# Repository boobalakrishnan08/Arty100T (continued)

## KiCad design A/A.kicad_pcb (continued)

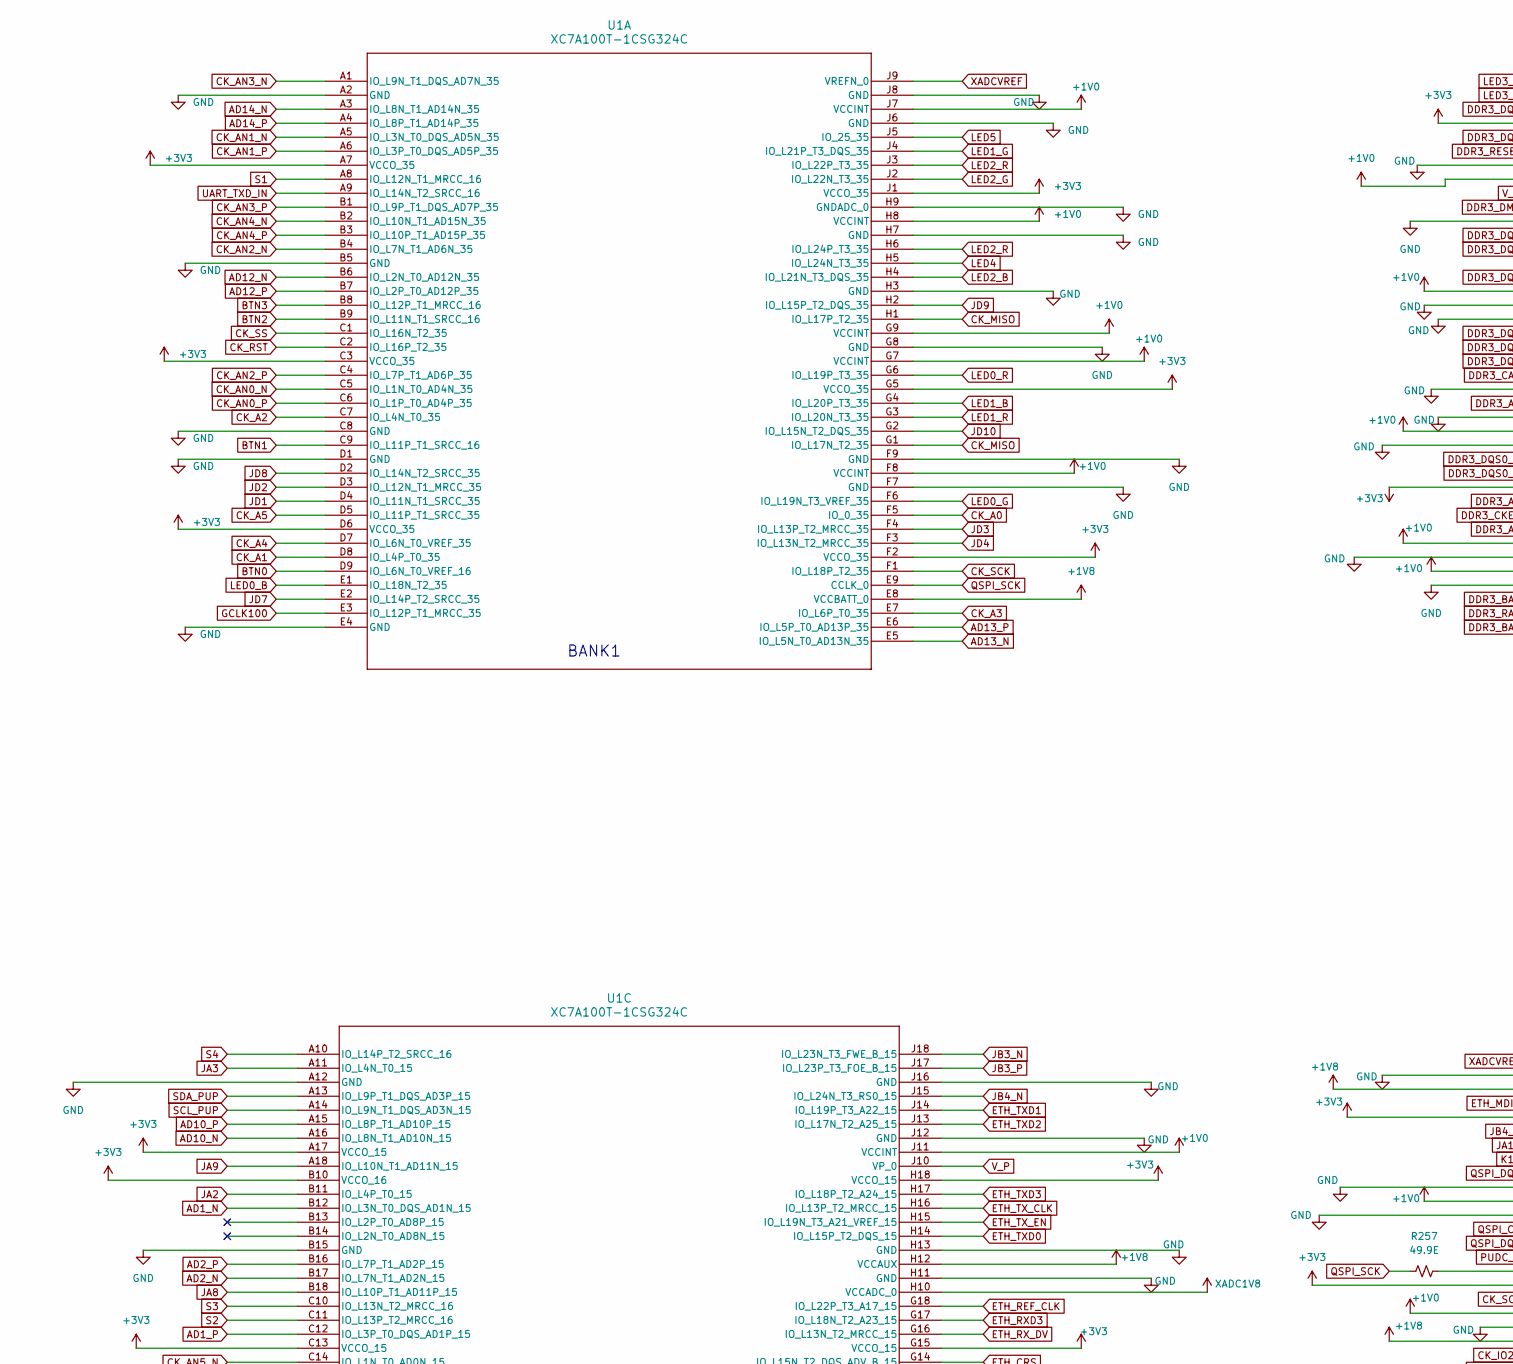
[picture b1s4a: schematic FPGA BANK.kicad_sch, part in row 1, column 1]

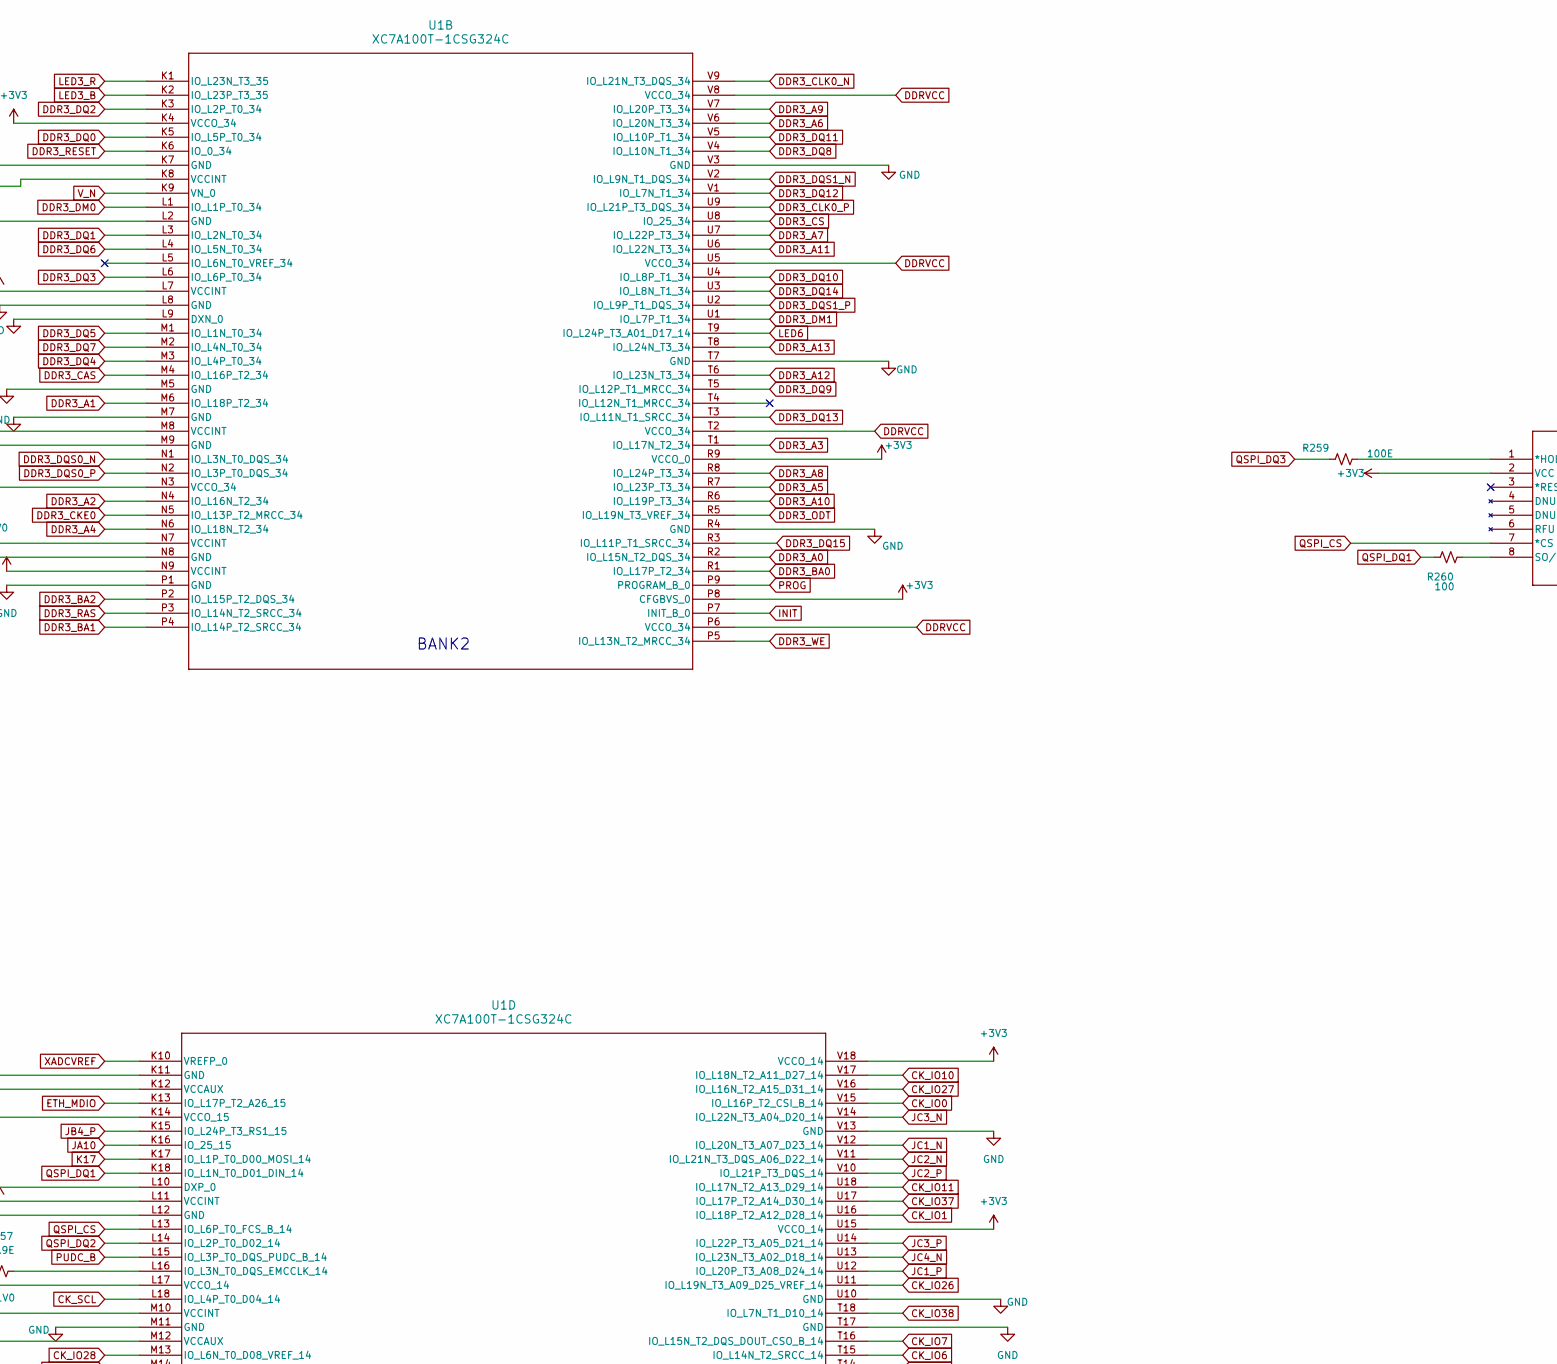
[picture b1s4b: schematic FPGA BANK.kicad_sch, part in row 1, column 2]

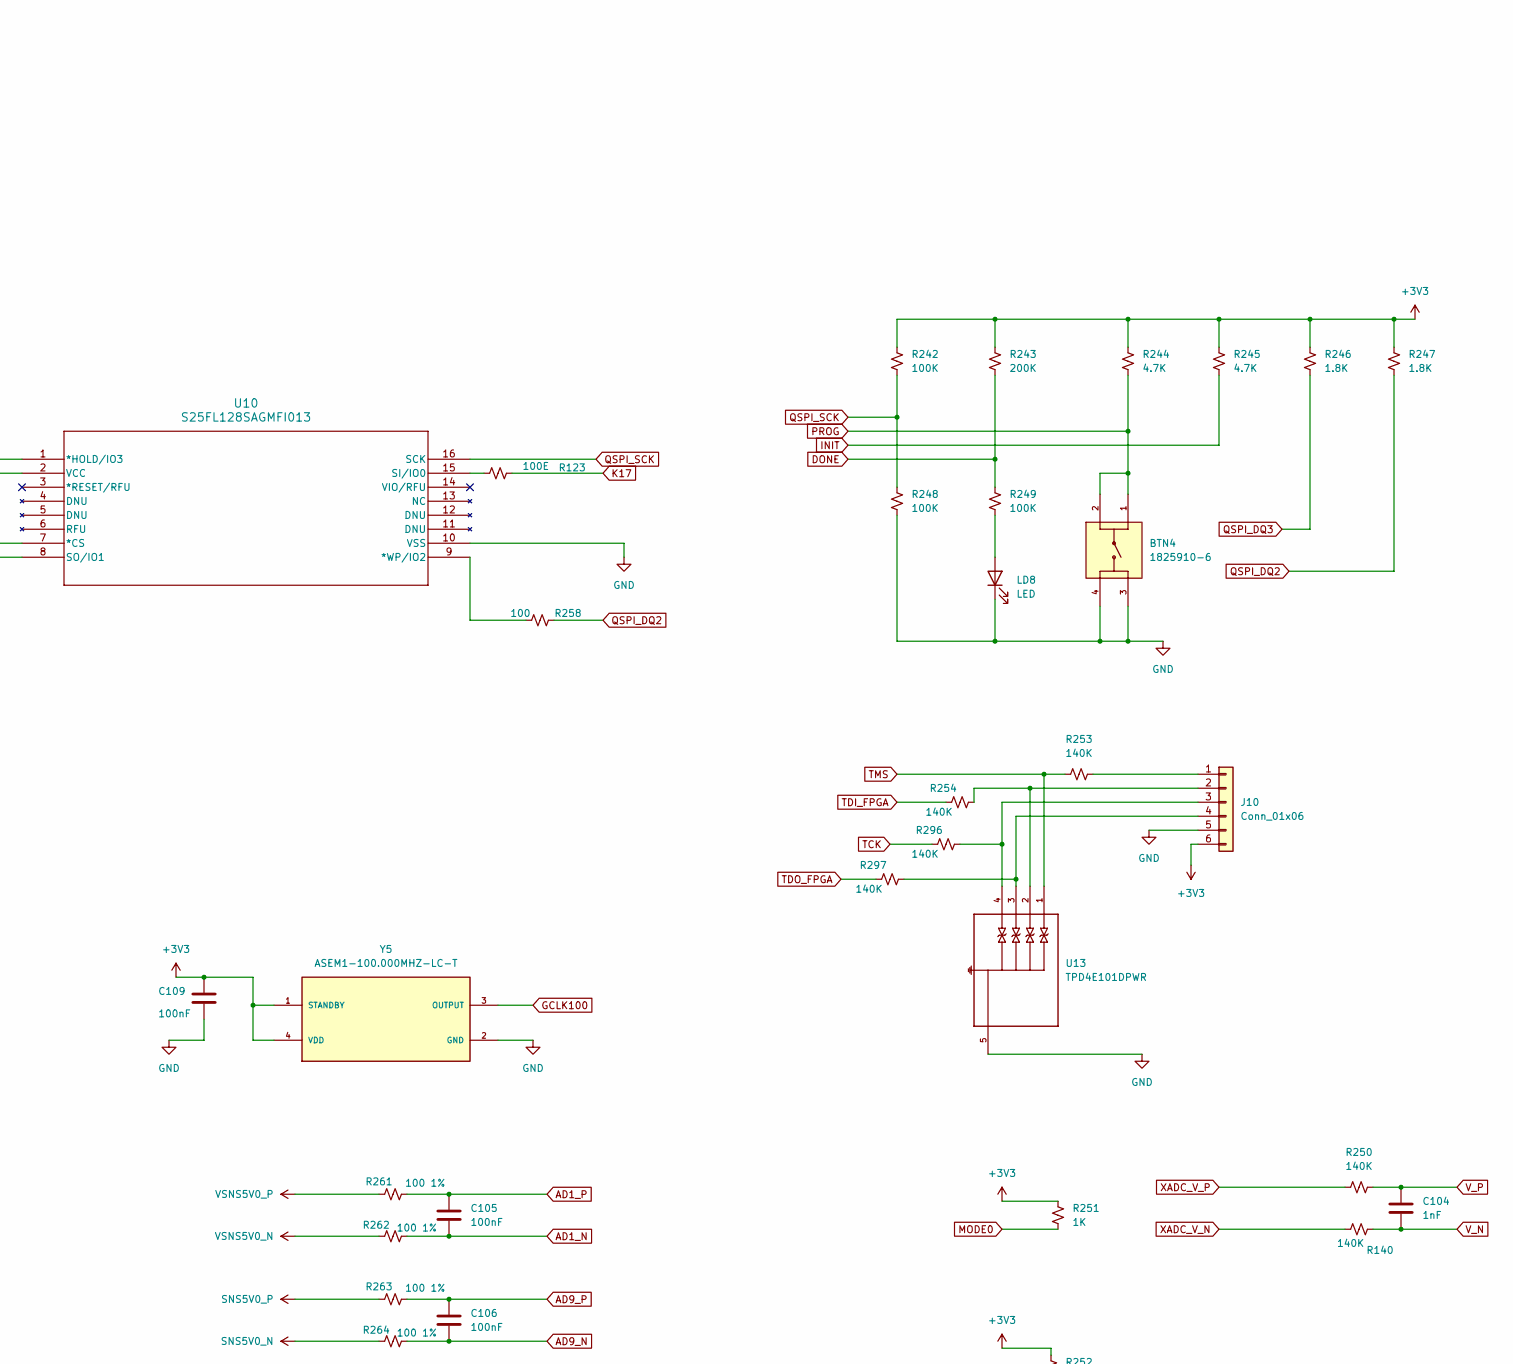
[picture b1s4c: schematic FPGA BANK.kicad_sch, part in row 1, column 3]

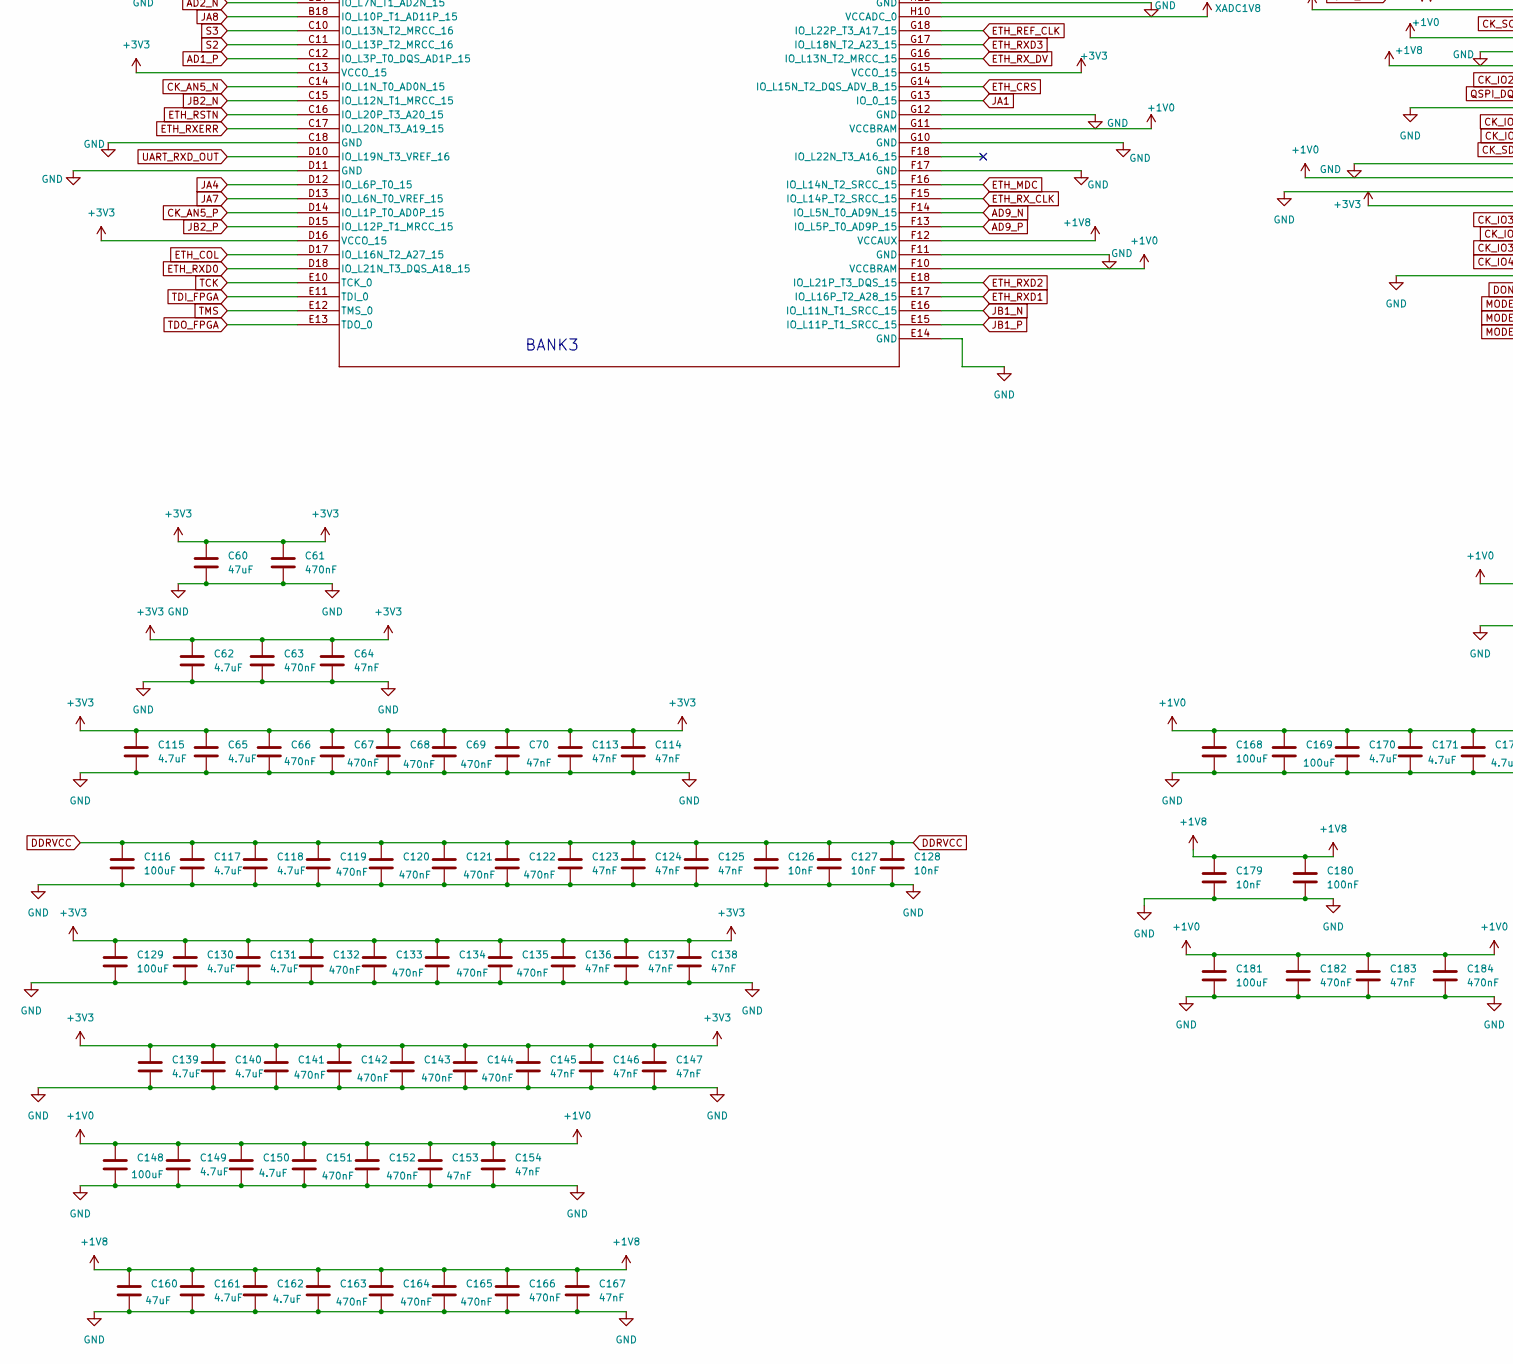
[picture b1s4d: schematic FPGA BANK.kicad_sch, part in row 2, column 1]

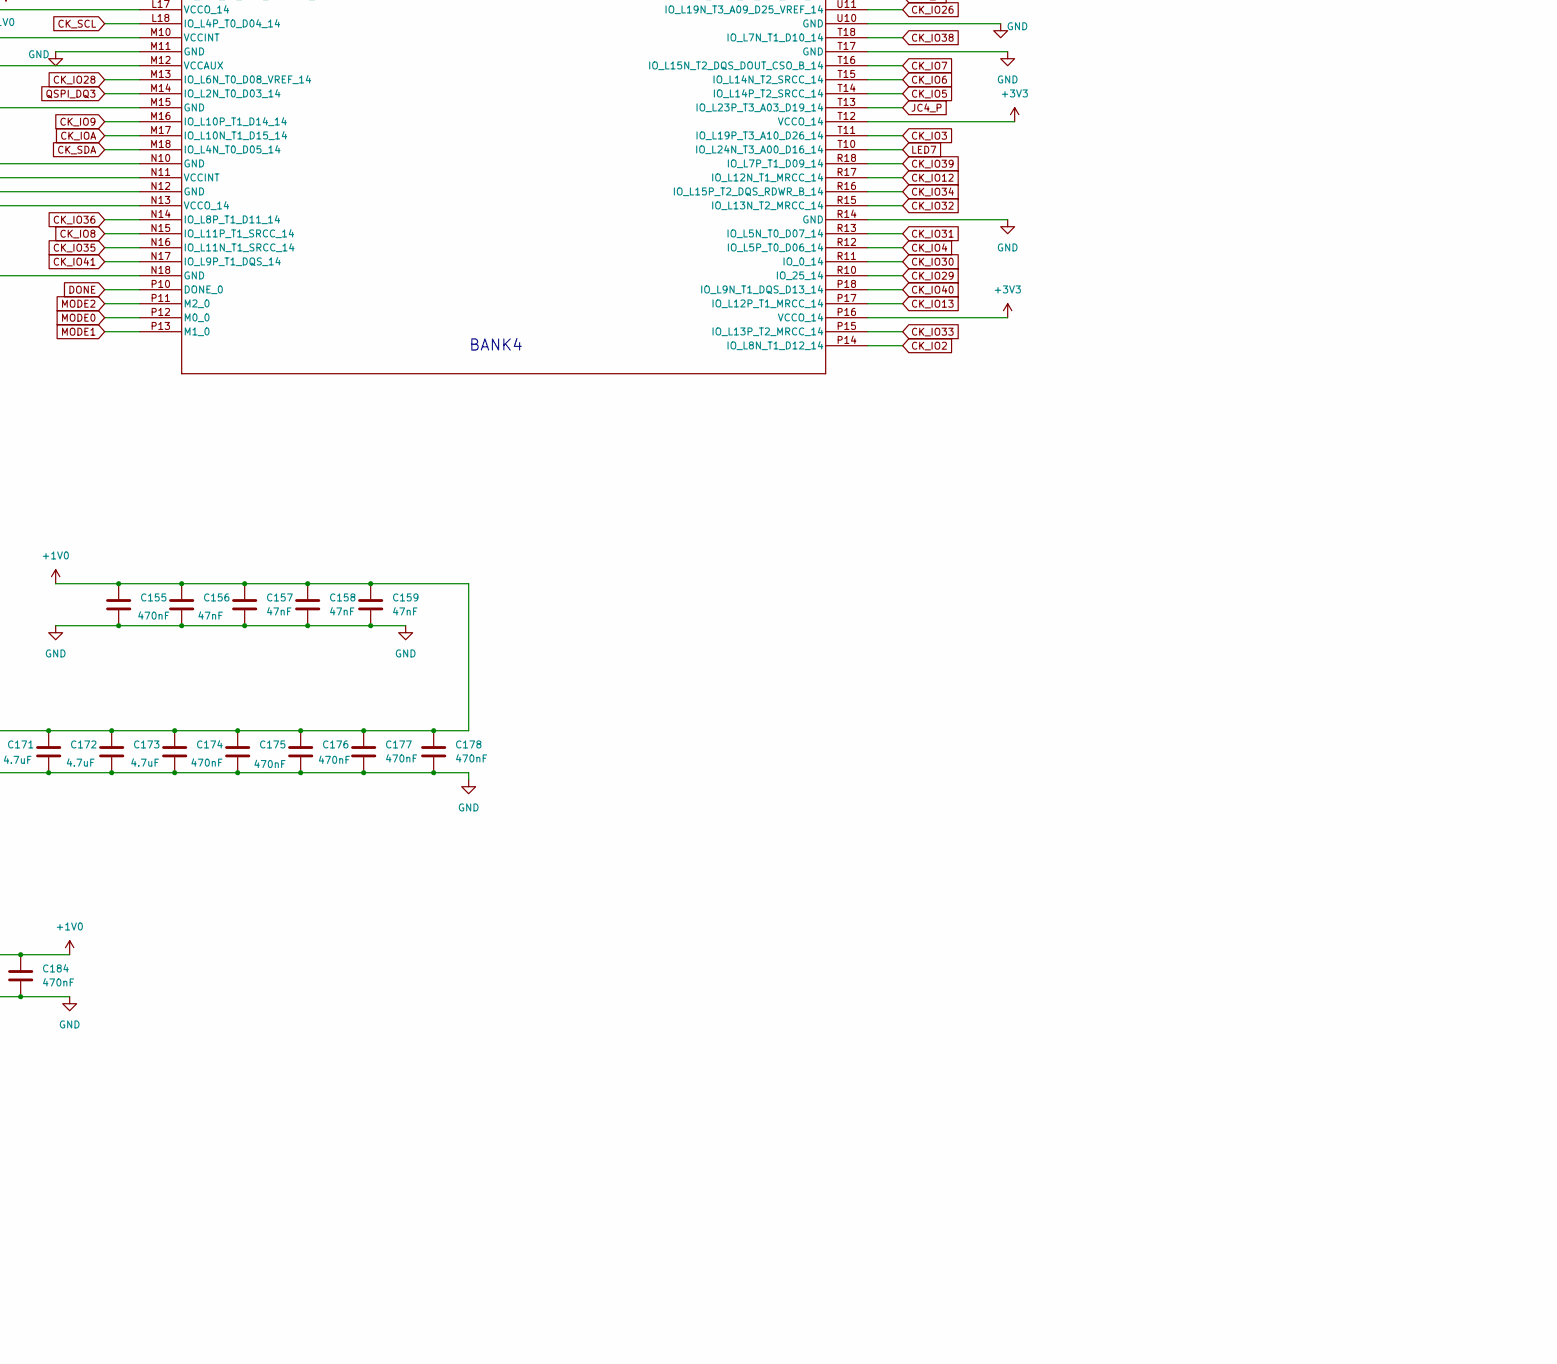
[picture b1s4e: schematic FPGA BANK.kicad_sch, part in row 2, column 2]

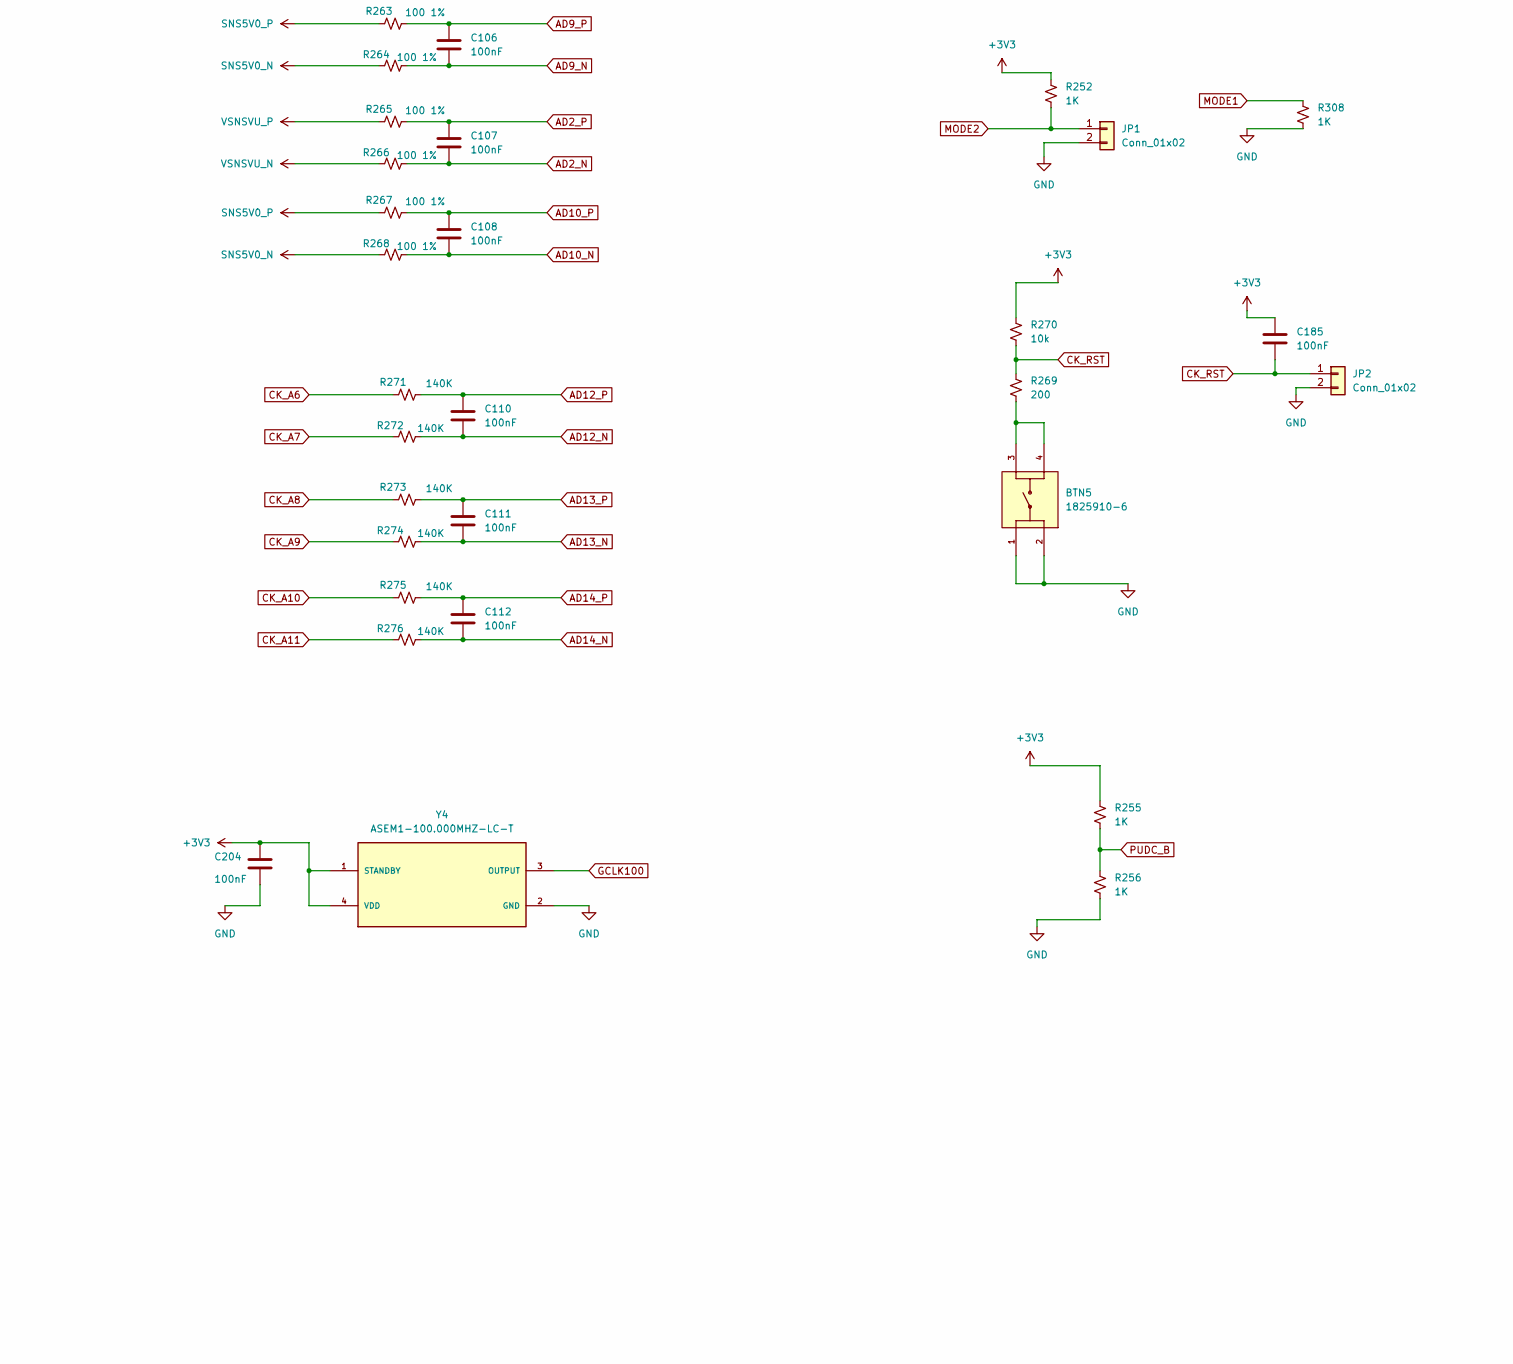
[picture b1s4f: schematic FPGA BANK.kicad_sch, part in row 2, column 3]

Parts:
BTN4, BTN5: 1825910-6; SW_1825910-6-4; PARTREV C10
C60, C160: 47uF; C_1210_3225Metric
C61, C63, C66, C67, C68, C69, C119, C120, C121, C122, C132, C133, C134, C135, C141, C142, C143, C144, C151, C152, C155, C163, C164, C165, C166, C174, C175, C176, C177, C178, C182, C184: 470nF; C_0603_1608Metric
C62, C65, C115, C117, C118, C130, C131, C139, C140, C149, C150, C161, C162, C170, C171, C172, C173: 4.7uF; C_0805_2012Metric
C64, C70, C113, C114, C123, C124, C125, C136, C137, C138, C145, C146, C147, C153, C154, C156, C157, C158, C159, C167, C183: 47nF; C_1206_3216Metric
C104: 1nF; C_1206_3216Metric
C105: 100nF; C_0603_1608Metric_Pad1.08x0.95mm_HandSolder
C106, C107, C108, C109, C110, C111, C112: 100nF; C_0402_1005Metric
C116, C129, C148, C168, C169, C181: 100uF; C_1206_3216Metric
C126, C127, C128, C179: 10nF; C_0201_0603Metric
C180: 100nF; C_0201_0603Metric
C185: 100nF; C_0805_2012Metric
C204: 100nF; C_1206_3216Metric
J10: Conn_01x06; PinSocket_1x06_P2.54mm_Vertical
JP1, JP2: Conn_01x02; PinHeader_1x02_P1.00mm_Vertical
LD8: LED; LED_01005_0402Metric
R123, R259: 100E; R_0402_1005Metric
R140, R250, R253, R254, R271, R272, R273, R274, R275, R276, R296, R297: 140K; R_0402_1005Metric
R242, R248, R249: 100K; R_0402_1005Metric
R243: 200K; R_0402_1005Metric
R244, R245: 4.7K; R_0402_1005Metric
R246, R247: 1.8K; R_0402_1005Metric
R251, R252, R255, R256, R308: 1K; R_0402_1005Metric
R257: 49.9E; R_0402_1005Metric
R258, R260: 100; R_0402_1005Metric
R261, R262, R263, R264, R265, R266, R267, R268: 100 1%; R_0402_1005Metric
R269: 200; R_0402_1005Metric
R270: 10k; R_0402_1005Metric
U1: XC7A100T-1CSG324C; BGA324C100P18X18_1900X1900X170
U10: S25FL128SAGMFI013; SO3016_SPA
U13: TPD4E101DPWR; IC_TPD4E101DPWR; PARTREV E
Y4, Y5: ASEM1-100.000MHZ-LC-T; XTAL_ASEM1-100.000MHZ-LC-T; PARTREV 1.4.2021

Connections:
+1V0: C148.1, C149.1, C150.1, C151.1, C152.1, C153.1, C154.1, C155.1, C156.1, C157.1, C158.1, C159.1, C168.1, C169.1, C170.1, C171.1, C172.1, C173.1, C174.1, C175.1, C176.1, C177.1, C178.1, C181.1, C182.1, C183.1, C184.1, U1.F8 (VCCINT), U1.F10 (VCCBRAM), U1.G7 (VCCINT), U1.G9 (VCCINT), U1.G11 (VCCBRAM), U1.H8 (VCCINT), U1.J7 (VCCINT), U1.J11 (VCCINT), U1.K8 (VCCINT), U1.L7 (VCCINT), U1.L11 (VCCINT), U1.M8 (VCCINT), U1.M10 (VCCINT), U1.N7 (VCCINT), U1.N9 (VCCINT), U1.N11 (VCCINT); also elsewhere on the board
+1V8: C160.1, C161.1, C162.1, C163.1, C164.1, C165.1, C166.1, C167.1, C179.1, C180.1, U1.E8 (VCCBATT_0), U1.F12 (VCCAUX), U1.H12 (VCCAUX), U1.K12 (VCCAUX), U1.M12 (VCCAUX); also elsewhere on the board
+3V3: C60.1, C61.1, C62.1, C63.1, C64.1, C65.1, C66.1, C67.1, C68.1, C69.1, C70.1, C109.1, C113.1, C114.1, C115.1, C129.1, C130.1, C131.1, C132.1, C133.1, C134.1, C135.1, C136.1, C137.1, C138.1, C139.1, C140.1, C141.1, C142.1, C143.1, C144.1, C145.1, C146.1, C147.1, C185.1, C204.1, J10.6, R242.1, R243.1, R244.1, R245.1, R246.1, R247.1, R251.2, R252.2, R255.2, R270.2, U1.A7 (VCCO_35), U1.A17 (VCCO_15), U1.B10 (VCCO_16), U1.C3 (VCCO_35), U1.C13 (VCCO_15), U1.D6 (VCCO_35), U1.D16 (VCCO_15), U1.F2 (VCCO_35), U1.G5 (VCCO_35), U1.G15 (VCCO_15), U1.H18 (VCCO_15), U1.J1 (VCCO_35), U1.K4 (VCCO_34), U1.K14 (VCCO_15), U1.L17 (VCCO_14), U1.N3 (VCCO_34), U1.N13 (VCCO_14), U1.P8 (CFGBVS_0), U1.P16 (VCCO_14), U1.R9 (VCCO_0), U1.T12 (VCCO_14), U1.U15 (VCCO_14), U1.V18 (VCCO_14), U10.2 (VCC), Y4.1 (STANDBY), Y4.4 (VDD), Y5.1 (STANDBY), Y5.4 (VDD); also elsewhere on the board
AD1_N: C105.2, R262.1, U1.B12 (IO_L3N_T0_DQS_AD1N_15)
AD1_P: C105.1, R261.1, U1.C12 (IO_L3P_T0_DQS_AD1P_15)
AD2_N: C107.2, R266.1, U1.B17 (IO_L7N_T1_AD2N_15)
AD2_P: C107.1, R265.1, U1.B16 (IO_L7P_T1_AD2P_15)
AD9_N: C106.2, R264.1, U1.F14 (IO_L5N_T0_AD9N_15)
AD9_P: C106.1, R263.1, U1.F13 (IO_L5P_T0_AD9P_15)
AD10_N: C108.2, R268.1, U1.A16 (IO_L8N_T1_AD10N_15)
AD10_P: C108.1, R267.1, U1.A15 (IO_L8P_T1_AD10P_15)
AD12_N: C110.2, R272.1, U1.B6 (IO_L2N_T0_AD12N_35)
AD12_P: C110.1, R271.1, U1.B7 (IO_L2P_T0_AD12P_35)
AD13_N: C111.2, R274.1, U1.E5 (IO_L5N_T0_AD13N_35)
AD13_P: C111.1, R273.1, U1.E6 (IO_L5P_T0_AD13P_35)
AD14_N: C112.2, R276.1, U1.A3 (IO_L8N_T1_AD14N_35)
AD14_P: C112.1, R275.1, U1.A4 (IO_L8P_T1_AD14P_35)
BTN0: U1.D9 (IO_L6N_T0_VREF_16); also elsewhere on the board
BTN1: U1.C9 (IO_L11P_T1_SRCC_16); also elsewhere on the board
BTN2: U1.B9 (IO_L11N_T1_SRCC_16); also elsewhere on the board
BTN3: U1.B8 (IO_L12P_T1_MRCC_16); also elsewhere on the board
CK_A0: U1.F5 (IO_0_35); also elsewhere on the board
CK_A1: U1.D8 (IO_L4P_T0_35); also elsewhere on the board
CK_A2: U1.C7 (IO_L4N_T0_35); also elsewhere on the board
CK_A3: U1.E7 (IO_L6P_T0_35); also elsewhere on the board
CK_A4: U1.D7 (IO_L6N_T0_VREF_35); also elsewhere on the board
CK_A5: U1.D5 (IO_L11P_T1_SRCC_35); also elsewhere on the board
CK_A6: R271.2; also elsewhere on the board
CK_A7: R272.2; also elsewhere on the board
CK_A8: R273.2; also elsewhere on the board
CK_A9: R274.2; also elsewhere on the board
CK_A10: R275.2; also elsewhere on the board
CK_A11: R276.2; also elsewhere on the board
CK_AN0_N: U1.C5 (IO_L1N_T0_AD4N_35); also elsewhere on the board
CK_AN0_P: U1.C6 (IO_L1P_T0_AD4P_35); also elsewhere on the board
CK_AN1_N: U1.A5 (IO_L3N_T0_DQS_AD5N_35); also elsewhere on the board
CK_AN1_P: U1.A6 (IO_L3P_T0_DQS_AD5P_35); also elsewhere on the board
CK_AN2_N: U1.B4 (IO_L7N_T1_AD6N_35); also elsewhere on the board
CK_AN2_P: U1.C4 (IO_L7P_T1_AD6P_35); also elsewhere on the board
CK_AN3_N: U1.A1 (IO_L9N_T1_DQS_AD7N_35); also elsewhere on the board
CK_AN3_P: U1.B1 (IO_L9P_T1_DQS_AD7P_35); also elsewhere on the board
CK_AN4_N: U1.B2 (IO_L10N_T1_AD15N_35); also elsewhere on the board
CK_AN4_P: U1.B3 (IO_L10P_T1_AD15P_35); also elsewhere on the board
CK_AN5_N: U1.C14 (IO_L1N_T0_AD0N_15); also elsewhere on the board
CK_AN5_P: U1.D14 (IO_L1P_T0_AD0P_15); also elsewhere on the board
CK_IO0: U1.V15 (IO_L16P_T2_CSI_B_14); also elsewhere on the board
CK_IO1: U1.U16 (IO_L18P_T2_A12_D28_14); also elsewhere on the board
CK_IO2: U1.P14 (IO_L8N_T1_D12_14); also elsewhere on the board
CK_IO3: U1.T11 (IO_L19P_T3_A10_D26_14); also elsewhere on the board
CK_IO4: U1.R12 (IO_L5P_T0_D06_14); also elsewhere on the board
CK_IO5: U1.T14 (IO_L14P_T2_SRCC_14); also elsewhere on the board
CK_IO6: U1.T15 (IO_L14N_T2_SRCC_14); also elsewhere on the board
CK_IO7: U1.T16 (IO_L15N_T2_DQS_DOUT_CSO_B_14); also elsewhere on the board
CK_IO8: U1.N15 (IO_L11P_T1_SRCC_14); also elsewhere on the board
CK_IO9: U1.M16 (IO_L10P_T1_D14_14); also elsewhere on the board
CK_IO10: U1.V17 (IO_L18N_T2_A11_D27_14); also elsewhere on the board
CK_IO11: U1.U18 (IO_L17N_T2_A13_D29_14); also elsewhere on the board
CK_IO12: U1.R17 (IO_L12N_T1_MRCC_14); also elsewhere on the board
CK_IO13: U1.P17 (IO_L12P_T1_MRCC_14); also elsewhere on the board
CK_IO26: U1.U11 (IO_L19N_T3_A09_D25_VREF_14); also elsewhere on the board
CK_IO27: U1.V16 (IO_L16N_T2_A15_D31_14); also elsewhere on the board
CK_IO28: U1.M13 (IO_L6N_T0_D08_VREF_14); also elsewhere on the board
CK_IO29: U1.R10 (IO_25_14); also elsewhere on the board
CK_IO30: U1.R11 (IO_0_14); also elsewhere on the board
CK_IO31: U1.R13 (IO_L5N_T0_D07_14); also elsewhere on the board
CK_IO32: U1.R15 (IO_L13N_T2_MRCC_14); also elsewhere on the board
CK_IO33: U1.P15 (IO_L13P_T2_MRCC_14); also elsewhere on the board
CK_IO34: U1.R16 (IO_L15P_T2_DQS_RDWR_B_14); also elsewhere on the board
CK_IO35: U1.N16 (IO_L11N_T1_SRCC_14); also elsewhere on the board
CK_IO36: U1.N14 (IO_L8P_T1_D11_14); also elsewhere on the board
CK_IO37: U1.U17 (IO_L17P_T2_A14_D30_14); also elsewhere on the board
CK_IO38: U1.T18 (IO_L7N_T1_D10_14); also elsewhere on the board
CK_IO39: U1.R18 (IO_L7P_T1_D09_14); also elsewhere on the board
CK_IO40: U1.P18 (IO_L9N_T1_DQS_D13_14); also elsewhere on the board
CK_IO41: U1.N17 (IO_L9P_T1_DQS_14); also elsewhere on the board
CK_IOA: U1.M17 (IO_L10N_T1_D15_14); also elsewhere on the board
CK_MISO: U1.G1 (IO_L17N_T2_35), U1.H1 (IO_L17P_T2_35); also elsewhere on the board
CK_RST: C185.2, JP2.1, R269.2, R270.1, U1.C2 (IO_L16P_T2_35); also elsewhere on the board
CK_SCK: U1.F1 (IO_L18P_T2_35); also elsewhere on the board
CK_SCL: U1.L18 (IO_L4P_T0_D04_14); also elsewhere on the board
CK_SDA: U1.M18 (IO_L4N_T0_D05_14); also elsewhere on the board
CK_SS: U1.C1 (IO_L16N_T2_35); also elsewhere on the board
DDR3_A0: U1.R2 (IO_L15N_T2_DQS_34); also elsewhere on the board
DDR3_A1: U1.M6 (IO_L18P_T2_34); also elsewhere on the board
DDR3_A2: U1.N4 (IO_L16N_T2_34); also elsewhere on the board
DDR3_A3: U1.T1 (IO_L17N_T2_34); also elsewhere on the board
DDR3_A4: U1.N6 (IO_L18N_T2_34); also elsewhere on the board
DDR3_A5: U1.R7 (IO_L23P_T3_34); also elsewhere on the board
DDR3_A6: U1.V6 (IO_L20N_T3_34); also elsewhere on the board
DDR3_A7: U1.U7 (IO_L22P_T3_34); also elsewhere on the board
DDR3_A8: U1.R8 (IO_L24P_T3_34); also elsewhere on the board
DDR3_A9: U1.V7 (IO_L20P_T3_34); also elsewhere on the board
DDR3_A10: U1.R6 (IO_L19P_T3_34); also elsewhere on the board
DDR3_A11: U1.U6 (IO_L22N_T3_34); also elsewhere on the board
DDR3_A12: U1.T6 (IO_L23N_T3_34); also elsewhere on the board
DDR3_A13: U1.T8 (IO_L24N_T3_34); also elsewhere on the board
DDR3_BA0: U1.R1 (IO_L17P_T2_34); also elsewhere on the board
DDR3_BA1: U1.P4 (IO_L14P_T2_SRCC_34); also elsewhere on the board
DDR3_BA2: U1.P2 (IO_L15P_T2_DQS_34); also elsewhere on the board
DDR3_CAS: U1.M4 (IO_L16P_T2_34); also elsewhere on the board
DDR3_CKE0: U1.N5 (IO_L13P_T2_MRCC_34); also elsewhere on the board
DDR3_CLK0_N: U1.V9 (IO_L21N_T3_DQS_34); also elsewhere on the board
DDR3_CLK0_P: U1.U9 (IO_L21P_T3_DQS_34); also elsewhere on the board
DDR3_CS: U1.U8 (IO_25_34); also elsewhere on the board
DDR3_DM0: U1.L1 (IO_L1P_T0_34); also elsewhere on the board
DDR3_DM1: U1.U1 (IO_L7P_T1_34); also elsewhere on the board
DDR3_DQ0: U1.K5 (IO_L5P_T0_34); also elsewhere on the board
DDR3_DQ1: U1.L3 (IO_L2N_T0_34); also elsewhere on the board
DDR3_DQ2: U1.K3 (IO_L2P_T0_34); also elsewhere on the board
DDR3_DQ3: U1.L6 (IO_L6P_T0_34); also elsewhere on the board
DDR3_DQ4: U1.M3 (IO_L4P_T0_34); also elsewhere on the board
DDR3_DQ5: U1.M1 (IO_L1N_T0_34); also elsewhere on the board
DDR3_DQ6: U1.L4 (IO_L5N_T0_34); also elsewhere on the board
DDR3_DQ7: U1.M2 (IO_L4N_T0_34); also elsewhere on the board
DDR3_DQ8: U1.V4 (IO_L10N_T1_34); also elsewhere on the board
DDR3_DQ9: U1.T5 (IO_L12P_T1_MRCC_34); also elsewhere on the board
DDR3_DQ10: U1.U4 (IO_L8P_T1_34); also elsewhere on the board
DDR3_DQ11: U1.V5 (IO_L10P_T1_34); also elsewhere on the board
DDR3_DQ12: U1.V1 (IO_L7N_T1_34); also elsewhere on the board
DDR3_DQ13: U1.T3 (IO_L11N_T1_SRCC_34); also elsewhere on the board
DDR3_DQ14: U1.U3 (IO_L8N_T1_34); also elsewhere on the board
DDR3_DQ15: U1.R3 (IO_L11P_T1_SRCC_34); also elsewhere on the board
DDR3_DQS0_N: U1.N1 (IO_L3N_T0_DQS_34); also elsewhere on the board
DDR3_DQS0_P: U1.N2 (IO_L3P_T0_DQS_34); also elsewhere on the board
DDR3_DQS1_N: U1.V2 (IO_L9N_T1_DQS_34); also elsewhere on the board
DDR3_DQS1_P: U1.U2 (IO_L9P_T1_DQS_34); also elsewhere on the board
DDR3_ODT: U1.R5 (IO_L19N_T3_VREF_34); also elsewhere on the board
DDR3_RAS: U1.P3 (IO_L14N_T2_SRCC_34); also elsewhere on the board
DDR3_RESET: U1.K6 (IO_0_34); also elsewhere on the board
DDR3_WE: U1.P5 (IO_L13N_T2_MRCC_34); also elsewhere on the board
DDRVCC: C116.1, C117.1, C118.1, C119.1, C120.1, C121.1, C122.1, C123.1, C124.1, C125.1, C126.1, C127.1, C128.1, U1.P6 (VCCO_34), U1.T2 (VCCO_34), U1.U5 (VCCO_34), U1.V8 (VCCO_34); also elsewhere on the board
DONE: R243.2, R249.1, U1.P10 (DONE_0)
ETH_COL: U1.D17 (IO_L16N_T2_A27_15); also elsewhere on the board
ETH_CRS: U1.G14 (IO_L15N_T2_DQS_ADV_B_15); also elsewhere on the board
ETH_MDC: U1.F16 (IO_L14N_T2_SRCC_15); also elsewhere on the board
ETH_MDIO: U1.K13 (IO_L17P_T2_A26_15); also elsewhere on the board
ETH_REF_CLK: U1.G18 (IO_L22P_T3_A17_15); also elsewhere on the board
ETH_RSTN: U1.C16 (IO_L20P_T3_A20_15); also elsewhere on the board
ETH_RXD0: U1.D18 (IO_L21N_T3_DQS_A18_15); also elsewhere on the board
ETH_RXD1: U1.E17 (IO_L16P_T2_A28_15); also elsewhere on the board
ETH_RXD2: U1.E18 (IO_L21P_T3_DQS_15); also elsewhere on the board
ETH_RXD3: U1.G17 (IO_L18N_T2_A23_15); also elsewhere on the board
ETH_RXERR: U1.C17 (IO_L20N_T3_A19_15); also elsewhere on the board
ETH_RX_CLK: U1.F15 (IO_L14P_T2_SRCC_15); also elsewhere on the board
ETH_RX_DV: U1.G16 (IO_L13N_T2_MRCC_15); also elsewhere on the board
ETH_TXD0: U1.H14 (IO_L15P_T2_DQS_15); also elsewhere on the board
ETH_TXD1: U1.J14 (IO_L19P_T3_A22_15); also elsewhere on the board
ETH_TXD2: U1.J13 (IO_L17N_T2_A25_15); also elsewhere on the board
ETH_TXD3: U1.H17 (IO_L18P_T2_A24_15); also elsewhere on the board
ETH_TX_CLK: U1.H16 (IO_L13P_T2_MRCC_15); also elsewhere on the board
ETH_TX_EN: U1.H15 (IO_L19N_T3_A21_VREF_15); also elsewhere on the board
GCLK100: U1.E3 (IO_L12P_T1_MRCC_35), Y4.3 (OUTPUT), Y5.3 (OUTPUT)
GND: BTN4.3, BTN4.4, BTN5.1, BTN5.2, C60.2, C61.2, C62.2, C63.2, C64.2, C65.2, C66.2, C67.2, C68.2, C69.2, C70.2, C109.2, C113.2, C114.2, C115.2, C116.2, C117.2, C118.2, C119.2, C120.2, C121.2, C122.2, C123.2, C124.2, C125.2, C126.2, C127.2, C128.2, C129.2, C130.2, C131.2, C132.2, C133.2, C134.2, C135.2, C136.2, C137.2, C138.2, C139.2, C140.2, C141.2, C142.2, C143.2, C144.2, C145.2, C146.2, C147.2, C148.2, C149.2, C150.2, C151.2, C152.2, C153.2, C154.2, C155.2, C156.2, C157.2, C158.2, C159.2, C160.2, C161.2, C162.2, C163.2, C164.2, C165.2, C166.2, C167.2, C168.2, C169.2, C170.2, C171.2, C172.2, C173.2, C174.2, C175.2, C176.2, C177.2, C178.2, C179.2, C180.2, C181.2, C182.2, C183.2, C184.2, C204.2, J10.5, JP1.2, JP2.2, LD8.1 (K), R248.2, R256.1, R308.1, U1.A2 (GND), U1.A12 (GND), U1.B5 (GND), U1.B15 (GND), U1.C8 (GND), U1.C18 (GND), U1.D1 (GND), U1.D11 (GND), U1.E4 (GND), U1.E14 (GND), U1.F7 (GND), U1.F9 (GND), U1.F11 (GND), U1.F17 (GND), U1.G8 (GND), U1.G10 (GND), U1.G12 (GND), U1.H3 (GND), U1.H7 (GND), U1.H9 (GNDADC_0), U1.H11 (GND), U1.H13 (GND), U1.J6 (GND), U1.J8 (GND), U1.J12 (GND), U1.J16 (GND), U1.K7 (GND), U1.K11 (GND), U1.L2 (GND), U1.L8 (GND), U1.L9 (DXN_0), U1.L10 (DXP_0), U1.L12 (GND), U1.M5 (GND), U1.M7 (GND), U1.M9 (GND), U1.M11 (GND), U1.M15 (GND), U1.N8 (GND), U1.N10 (GND), U1.N12 (GND), U1.N18 (GND), U1.P1 (GND), U1.R4 (GND), U1.R14 (GND), U1.T7 (GND), U1.T17 (GND), U1.U10 (GND), U1.V3 (GND), U1.V13 (GND), U10.10 (VSS), U13.5, Y4.2 (GND), Y5.2 (GND); also elsewhere on the board
INIT: R245.2, U1.P7 (INIT_B_0)
JA1: U1.G13 (IO_0_15); also elsewhere on the board
JA2: U1.B11 (IO_L4P_T0_15); also elsewhere on the board
JA3: U1.A11 (IO_L4N_T0_15); also elsewhere on the board
JA4: U1.D12 (IO_L6P_T0_15); also elsewhere on the board
JA7: U1.D13 (IO_L6N_T0_VREF_15); also elsewhere on the board
JA8: U1.B18 (IO_L10P_T1_AD11P_15); also elsewhere on the board
JA9: U1.A18 (IO_L10N_T1_AD11N_15); also elsewhere on the board
JA10: U1.K16 (IO_25_15); also elsewhere on the board
JB1_N: U1.E16 (IO_L11N_T1_SRCC_15); also elsewhere on the board
JB1_P: U1.E15 (IO_L11P_T1_SRCC_15); also elsewhere on the board
JB2_N: U1.C15 (IO_L12N_T1_MRCC_15); also elsewhere on the board
JB2_P: U1.D15 (IO_L12P_T1_MRCC_15); also elsewhere on the board
JB3_N: U1.J18 (IO_L23N_T3_FWE_B_15); also elsewhere on the board
JB3_P: U1.J17 (IO_L23P_T3_FOE_B_15); also elsewhere on the board
JB4_N: U1.J15 (IO_L24N_T3_RS0_15); also elsewhere on the board
JB4_P: U1.K15 (IO_L24P_T3_RS1_15); also elsewhere on the board
JC1_N: U1.V12 (IO_L20N_T3_A07_D23_14); also elsewhere on the board
JC1_P: U1.U12 (IO_L20P_T3_A08_D24_14); also elsewhere on the board
JC2_N: U1.V11 (IO_L21N_T3_DQS_A06_D22_14); also elsewhere on the board
JC2_P: U1.V10 (IO_L21P_T3_DQS_14); also elsewhere on the board
JC3_N: U1.V14 (IO_L22N_T3_A04_D20_14); also elsewhere on the board
JC3_P: U1.U14 (IO_L22P_T3_A05_D21_14); also elsewhere on the board
JC4_N: U1.U13 (IO_L23N_T3_A02_D18_14); also elsewhere on the board
JC4_P: U1.T13 (IO_L23P_T3_A03_D19_14); also elsewhere on the board
JD1: U1.D4 (IO_L11N_T1_SRCC_35); also elsewhere on the board
JD2: U1.D3 (IO_L12N_T1_MRCC_35); also elsewhere on the board
JD3: U1.F4 (IO_L13P_T2_MRCC_35); also elsewhere on the board
JD4: U1.F3 (IO_L13N_T2_MRCC_35); also elsewhere on the board
JD7: U1.E2 (IO_L14P_T2_SRCC_35); also elsewhere on the board
JD8: U1.D2 (IO_L14N_T2_SRCC_35); also elsewhere on the board
JD9: U1.H2 (IO_L15P_T2_DQS_35); also elsewhere on the board
JD10: U1.G2 (IO_L15N_T2_DQS_35); also elsewhere on the board
K17: R123.1, U1.K17 (IO_L1P_T0_D00_MOSI_14)
LED0_B: U1.E1 (IO_L18N_T2_35); also elsewhere on the board
LED0_G: U1.F6 (IO_L19N_T3_VREF_35); also elsewhere on the board
LED0_R: U1.G6 (IO_L19P_T3_35); also elsewhere on the board
LED1_B: U1.G4 (IO_L20P_T3_35); also elsewhere on the board
LED1_G: U1.J4 (IO_L21P_T3_DQS_35); also elsewhere on the board
LED1_R: U1.G3 (IO_L20N_T3_35); also elsewhere on the board
LED2_B: U1.H4 (IO_L21N_T3_DQS_35); also elsewhere on the board
LED2_G: U1.J2 (IO_L22N_T3_35); also elsewhere on the board
LED2_R: U1.H6 (IO_L24P_T3_35), U1.J3 (IO_L22P_T3_35); also elsewhere on the board
LED3_B: U1.K2 (IO_L23P_T3_35); also elsewhere on the board
LED3_R: U1.K1 (IO_L23N_T3_35); also elsewhere on the board
LED4: U1.H5 (IO_L24N_T3_35); also elsewhere on the board
LED5: U1.J5 (IO_25_35); also elsewhere on the board
LED6: U1.T9 (IO_L24P_T3_A01_D17_14); also elsewhere on the board
LED7: U1.T10 (IO_L24N_T3_A00_D16_14); also elsewhere on the board
MODE0: R251.1, U1.P12 (M0_0)
MODE1: R308.2, U1.P13 (M1_0)
MODE2: JP1.1, R252.1, U1.P11 (M2_0)
unnamed: BTN5.3, BTN5.4, R269.1
unnamed: J10.1, R253.2
unnamed: J10.2, R254.2, U13.2
unnamed: J10.3, R296.2, U13.4
unnamed: J10.4, R297.2, U13.3
unnamed: LD8.2 (A), R249.2
unnamed: R257.1, U1.L16 (IO_L3N_T0_DQS_EMCCLK_14)
unnamed: R259.1, U10.1 (*HOLD/IO3)
unnamed: R258.1, U10.9 (*WP/IO2)
unnamed: R123.2, U10.15 (SI/IO0)
unnamed: R260.2, U10.8 (SO/IO1)
PROG: BTN4.1, BTN4.2, R244.2, U1.P9 (PROGRAM_B_0)
PUDC_B: R255.1, R256.2, U1.L15 (IO_L3P_T0_DQS_PUDC_B_14)
QSPI_CS: U1.L13 (IO_L6P_T0_FCS_B_14), U10.7 (*CS)
QSPI_DQ1: R260.1, U1.K18 (IO_L1N_T0_D01_DIN_14)
QSPI_DQ2: R247.2, R258.2, U1.L14 (IO_L2P_T0_D02_14)
QSPI_DQ3: R246.2, R259.2, U1.M14 (IO_L2N_T0_D03_14)
QSPI_SCK: R242.2, R248.1, R257.2, U1.E9 (CCLK_0), U10.16 (SCK)
S1: U1.A8 (IO_L12N_T1_MRCC_16); also elsewhere on the board
S2: U1.C11 (IO_L13P_T2_MRCC_16); also elsewhere on the board
S3: U1.C10 (IO_L13N_T2_MRCC_16); also elsewhere on the board
S4: U1.A10 (IO_L14P_T2_SRCC_16); also elsewhere on the board
SCL_PUP: U1.A14 (IO_L9N_T1_DQS_AD3N_15); also elsewhere on the board
SDA_PUP: U1.A13 (IO_L9P_T1_DQS_AD3P_15); also elsewhere on the board
SNS5V0_N: R264.2, R268.2; also elsewhere on the board
SNS5V0_P: R263.2, R267.2; also elsewhere on the board
TCK: R296.1, U1.E10 (TCK_0); also elsewhere on the board
TDI_FPGA: R254.1, U1.E11 (TDI_0)
TDO_FPGA: R297.1, U1.E13 (TDO_0)
TMS: R253.1, U1.E12 (TMS_0), U13.1; also elsewhere on the board
UART_RXD_OUT: U1.D10 (IO_L19N_T3_VREF_16); also elsewhere on the board
UART_TXD_IN: U1.A9 (IO_L14N_T2_SRCC_16); also elsewhere on the board
VSNS5V0_N: R262.2; also elsewhere on the board
VSNS5V0_P: R261.2; also elsewhere on the board
VSNSVU_N: R266.2
VSNSVU_P: R265.2
V_N: C104.2, R140.2, U1.K9 (VN_0)
V_P: C104.1, R250.2, U1.J10 (VP_0)
XADC1V8: U1.H10 (VCCADC_0); also elsewhere on the board
XADCVREF: U1.J9 (VREFN_0), U1.K10 (VREFP_0); also elsewhere on the board
XADC_V_N: R140.1; also elsewhere on the board
XADC_V_P: R250.1; also elsewhere on the board

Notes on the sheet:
BANK1
BANK2
BANK3
BANK4
